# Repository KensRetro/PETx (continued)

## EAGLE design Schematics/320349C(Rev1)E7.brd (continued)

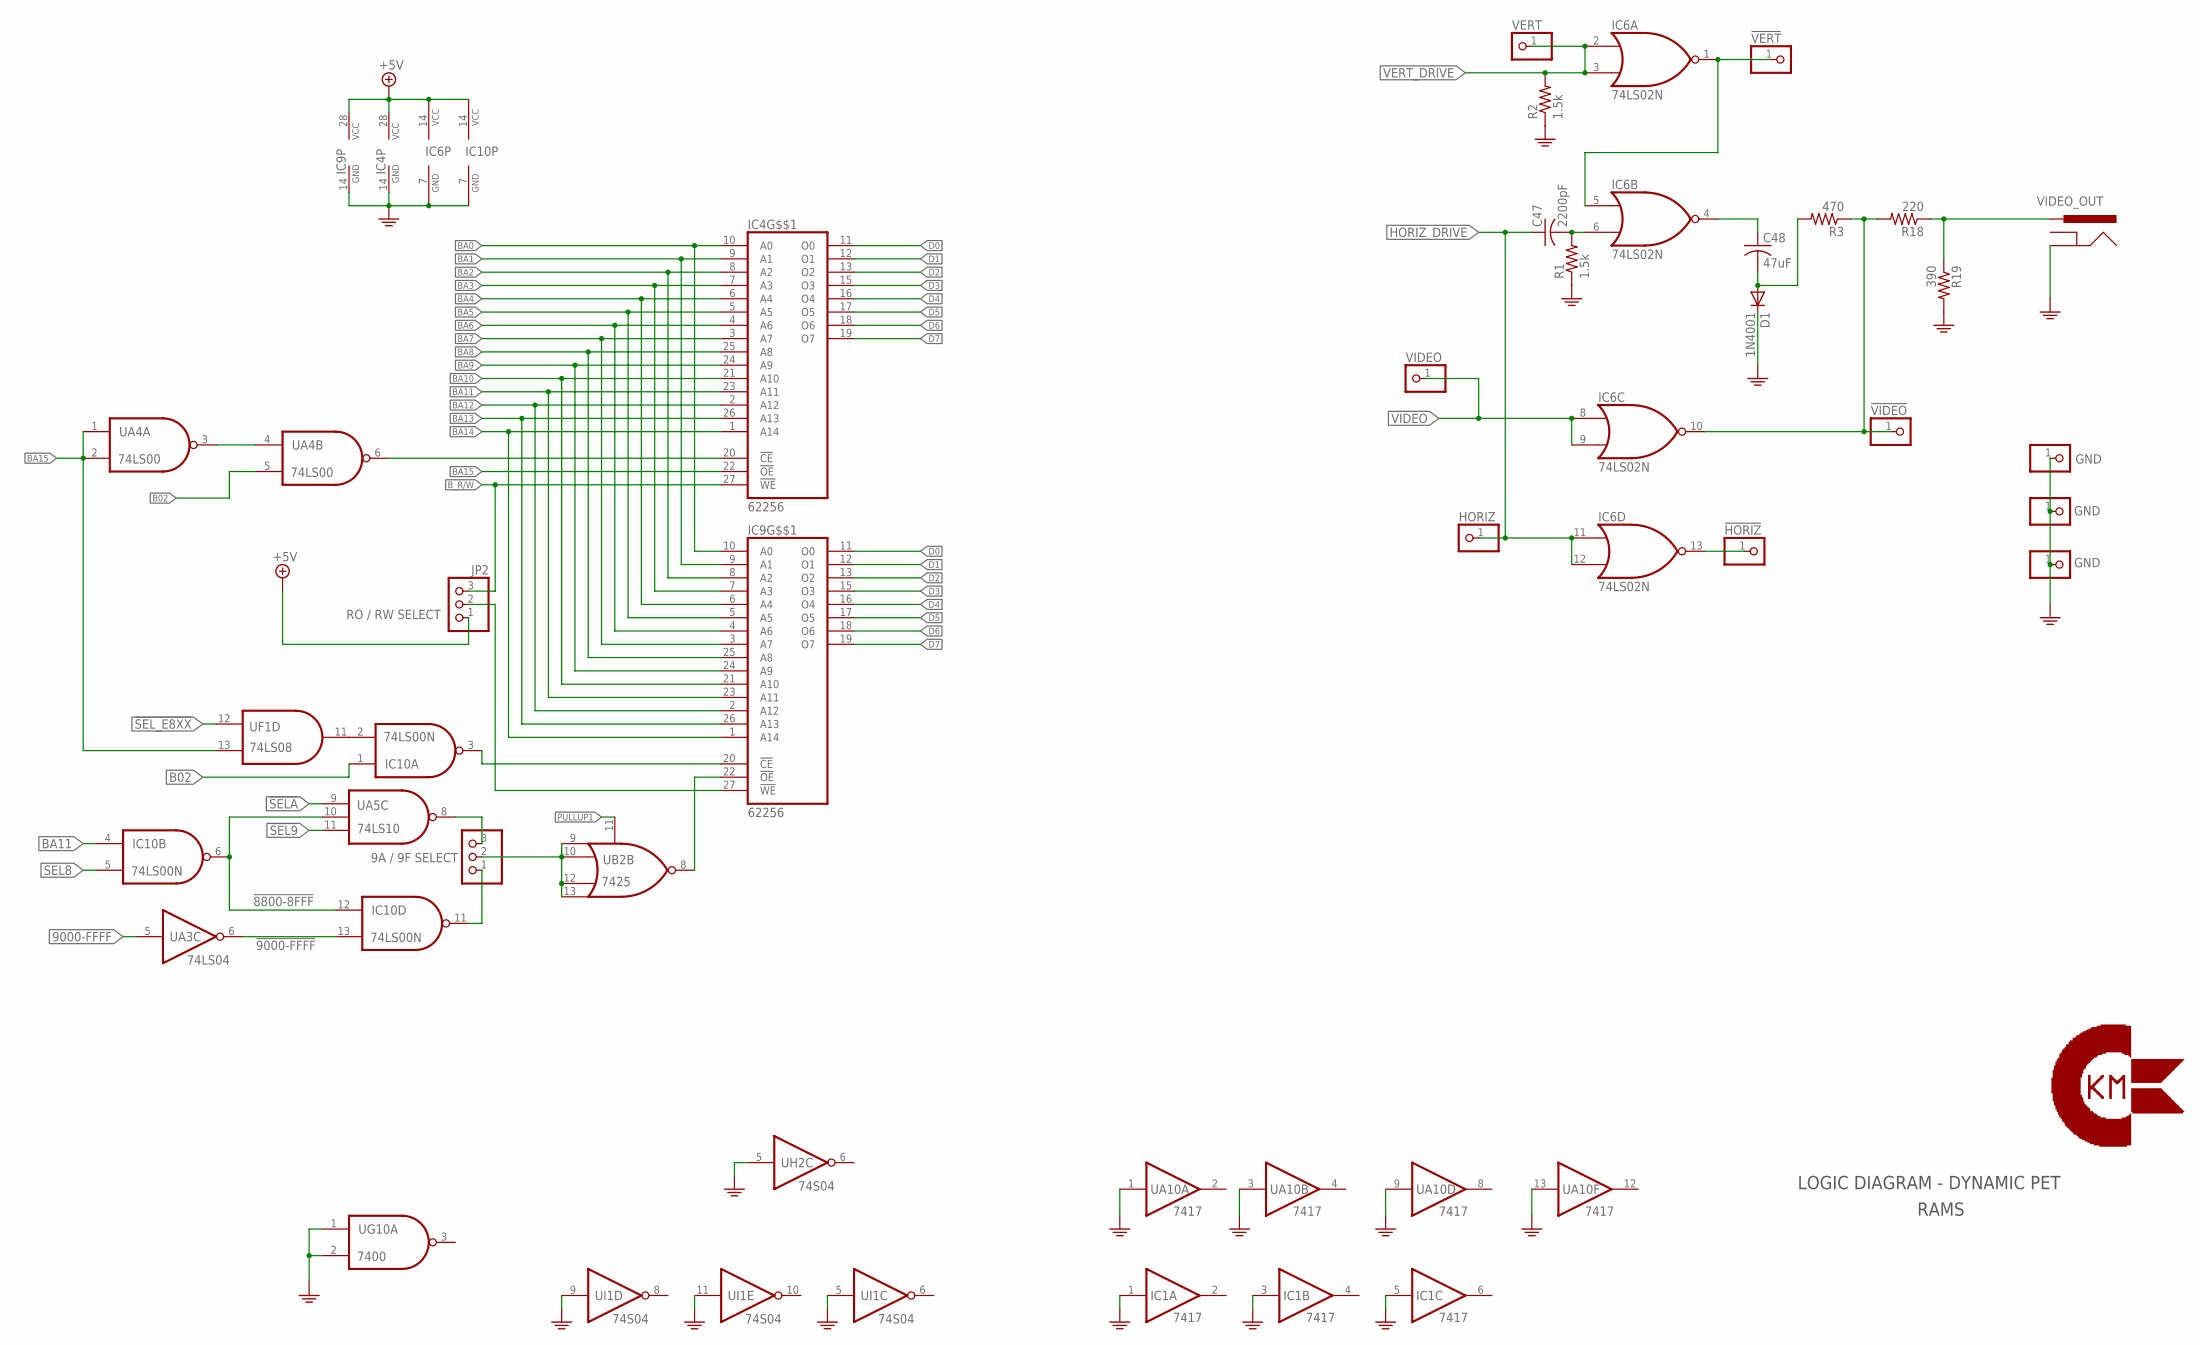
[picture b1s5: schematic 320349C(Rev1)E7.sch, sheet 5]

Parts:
!HORIZ: PINHD-1X1; 1X01
!VERT: PINHD-1X1; 1X01
!VIDEO: PINHD-1X1; 1X01
C47: 2200pF; C025-025X050
C48: 47uF; C050-035X075
D1: 1N4001; DO41-10
HGND: GND; 1X01
HORIZ: PINHD-1X1; 1X01
IC1: 7417; DIL14
IC4, IC9: 62256; DIL28
IC6: 74LS02N; DIL14
IC10: 74LS00N; DIL14
JP2: RO / RW SELECT; 1X03
JP3: 9A / 9F SELECT; 1X03
R1, R2: 1.5k; 0207/10
R3: 470; 0207/10
R18: 220; 0207/10
R19: 390; 0207/10
UA3: 74LS04; DIL14
UA4: 74LS00; DIL14
UA5: 74LS10; DIL14
UA10: 7417; DIL14
UB2: 7425; DIL14
UF1: 74LS08; DIL14
UG10: 7400; DIL14
UH2: 74S04; DIL14
UI1: 74S04; DIL14
VDGND: GND; 1X01
VERT: PINHD-1X1; 1X01
VGND: GND; 1X01
VIDEO: PINHD-1X1; 1X01
VIDEO_OUT: POWER_JACKRCA; RCA

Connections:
9000-FFFF: UA3.5 (I); also elsewhere on the board
!8800-8FFF: IC10.6 (O), IC10.12 (I0), UA5.10 (I1)
!9000-FFFF: IC10.13 (I1), UA3.6 (O)
!SEL9: UA5.11 (I2); also elsewhere on the board
!SELA: UA5.9 (I0); also elsewhere on the board
!SEL_E8XX: UF1.12 (I0); also elsewhere on the board
+5V: IC4.28 (VCC), IC6.14 (VCC), IC9.28 (VCC), IC10.14 (VCC), JP2.1; also elsewhere on the board
B02: IC10.1 (I0), UA4.5 (I1); also elsewhere on the board
BA0: IC4.10 (A0), IC9.10 (A0); also elsewhere on the board
BA1: IC4.9 (A1), IC9.9 (A1); also elsewhere on the board
BA2: IC4.8 (A2), IC9.8 (A2); also elsewhere on the board
BA3: IC4.7 (A3), IC9.7 (A3); also elsewhere on the board
BA4: IC4.6 (A4), IC9.6 (A4); also elsewhere on the board
BA5: IC4.5 (A5), IC9.5 (A5); also elsewhere on the board
BA6: IC4.4 (A6), IC9.4 (A6); also elsewhere on the board
BA7: IC4.3 (A7), IC9.3 (A7); also elsewhere on the board
BA8: IC4.25 (A8), IC9.25 (A8); also elsewhere on the board
BA9: IC4.24 (A9), IC9.24 (A9); also elsewhere on the board
BA10: IC4.21 (A10), IC9.21 (A10); also elsewhere on the board
BA11: IC4.23 (A11), IC9.23 (A11), IC10.4 (I0); also elsewhere on the board
BA12: IC4.2 (A12), IC9.2 (A12); also elsewhere on the board
BA13: IC4.26 (A13), IC9.26 (A13); also elsewhere on the board
BA14: IC4.1 (A14), IC9.1 (A14); also elsewhere on the board
BA15: IC4.22 (!OE), UA4.1 (I0), UA4.2 (I1), UF1.13 (I1); also elsewhere on the board
B_R/W: IC4.27 (!WE), JP2.3; also elsewhere on the board
D0: IC4.11 (O0), IC9.11 (O0); also elsewhere on the board
D1: IC4.12 (O1), IC9.12 (O1); also elsewhere on the board
D2: IC4.13 (O2), IC9.13 (O2); also elsewhere on the board
D3: IC4.15 (O3), IC9.15 (O3); also elsewhere on the board
D4: IC4.16 (O4), IC9.16 (O4); also elsewhere on the board
D5: IC4.17 (O5), IC9.17 (O5); also elsewhere on the board
D6: IC4.18 (O6), IC9.18 (O6); also elsewhere on the board
D7: IC4.19 (O7), IC9.19 (O7); also elsewhere on the board
GND: D1.C, HGND.1, IC1.1 (I), IC1.3 (I), IC1.5 (I), IC4.14 (GND), IC6.7 (GND), IC9.14 (GND), IC10.7 (GND), R1.1, R2.1, R19.2, UA10.1 (I), UA10.3 (I), UA10.9 (I), UA10.13 (I), UG10.1 (I0), UG10.2 (I1), UH2.5 (I), UI1.5 (I), UI1.9 (I), UI1.11 (I), VDGND.1, VGND.1, VIDEO_OUT.BARREL (GND); also elsewhere on the board
HORIZ_DRIVE: C47.1, HORIZ.1, IC6.11 (I0), IC6.12 (I1); also elsewhere on the board
unnamed: JP3.3, UA5.8 (O)
unnamed: !VERT.1, IC6.1 (O), IC6.5 (I0)
unnamed: IC10.2 (I1), UF1.11 (O)
unnamed: R18.1, R19.1, VIDEO_OUT.BREAK (PWR)
unnamed: C47.2, IC6.6 (I1), R1.2
unnamed: IC9.22 (!OE), UB2.8 (O)
unnamed: !VIDEO.1, IC6.10 (O), R3.1, R18.2
unnamed: JP3.2, UB2.9 (I0), UB2.10 (I1), UB2.12 (I2), UB2.13 (I3)
unnamed: C48.1, IC6.4 (O)
unnamed: C48.2, D1.A, R3.2
unnamed: IC9.20 (!CE), IC10.3 (O)
unnamed: IC9.27 (!WE), JP2.2
unnamed: !HORIZ.1, IC6.13 (O)
unnamed: IC4.20 (!CE), UA4.6 (O)
unnamed: IC10.11 (O), JP3.1
unnamed: UA4.3 (O), UA4.4 (I0)
PULLUP1: UB2.11 (G); also elsewhere on the board
SEL8: IC10.5 (I1); also elsewhere on the board
VERT_DRIVE: IC6.2 (I0), IC6.3 (I1), R2.2, VERT.1; also elsewhere on the board
VIDEO: IC6.8 (I0), IC6.9 (I1), VIDEO.1; also elsewhere on the board

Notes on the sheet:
LOGIC DIAGRAM - DYNAMIC PET
RAMS

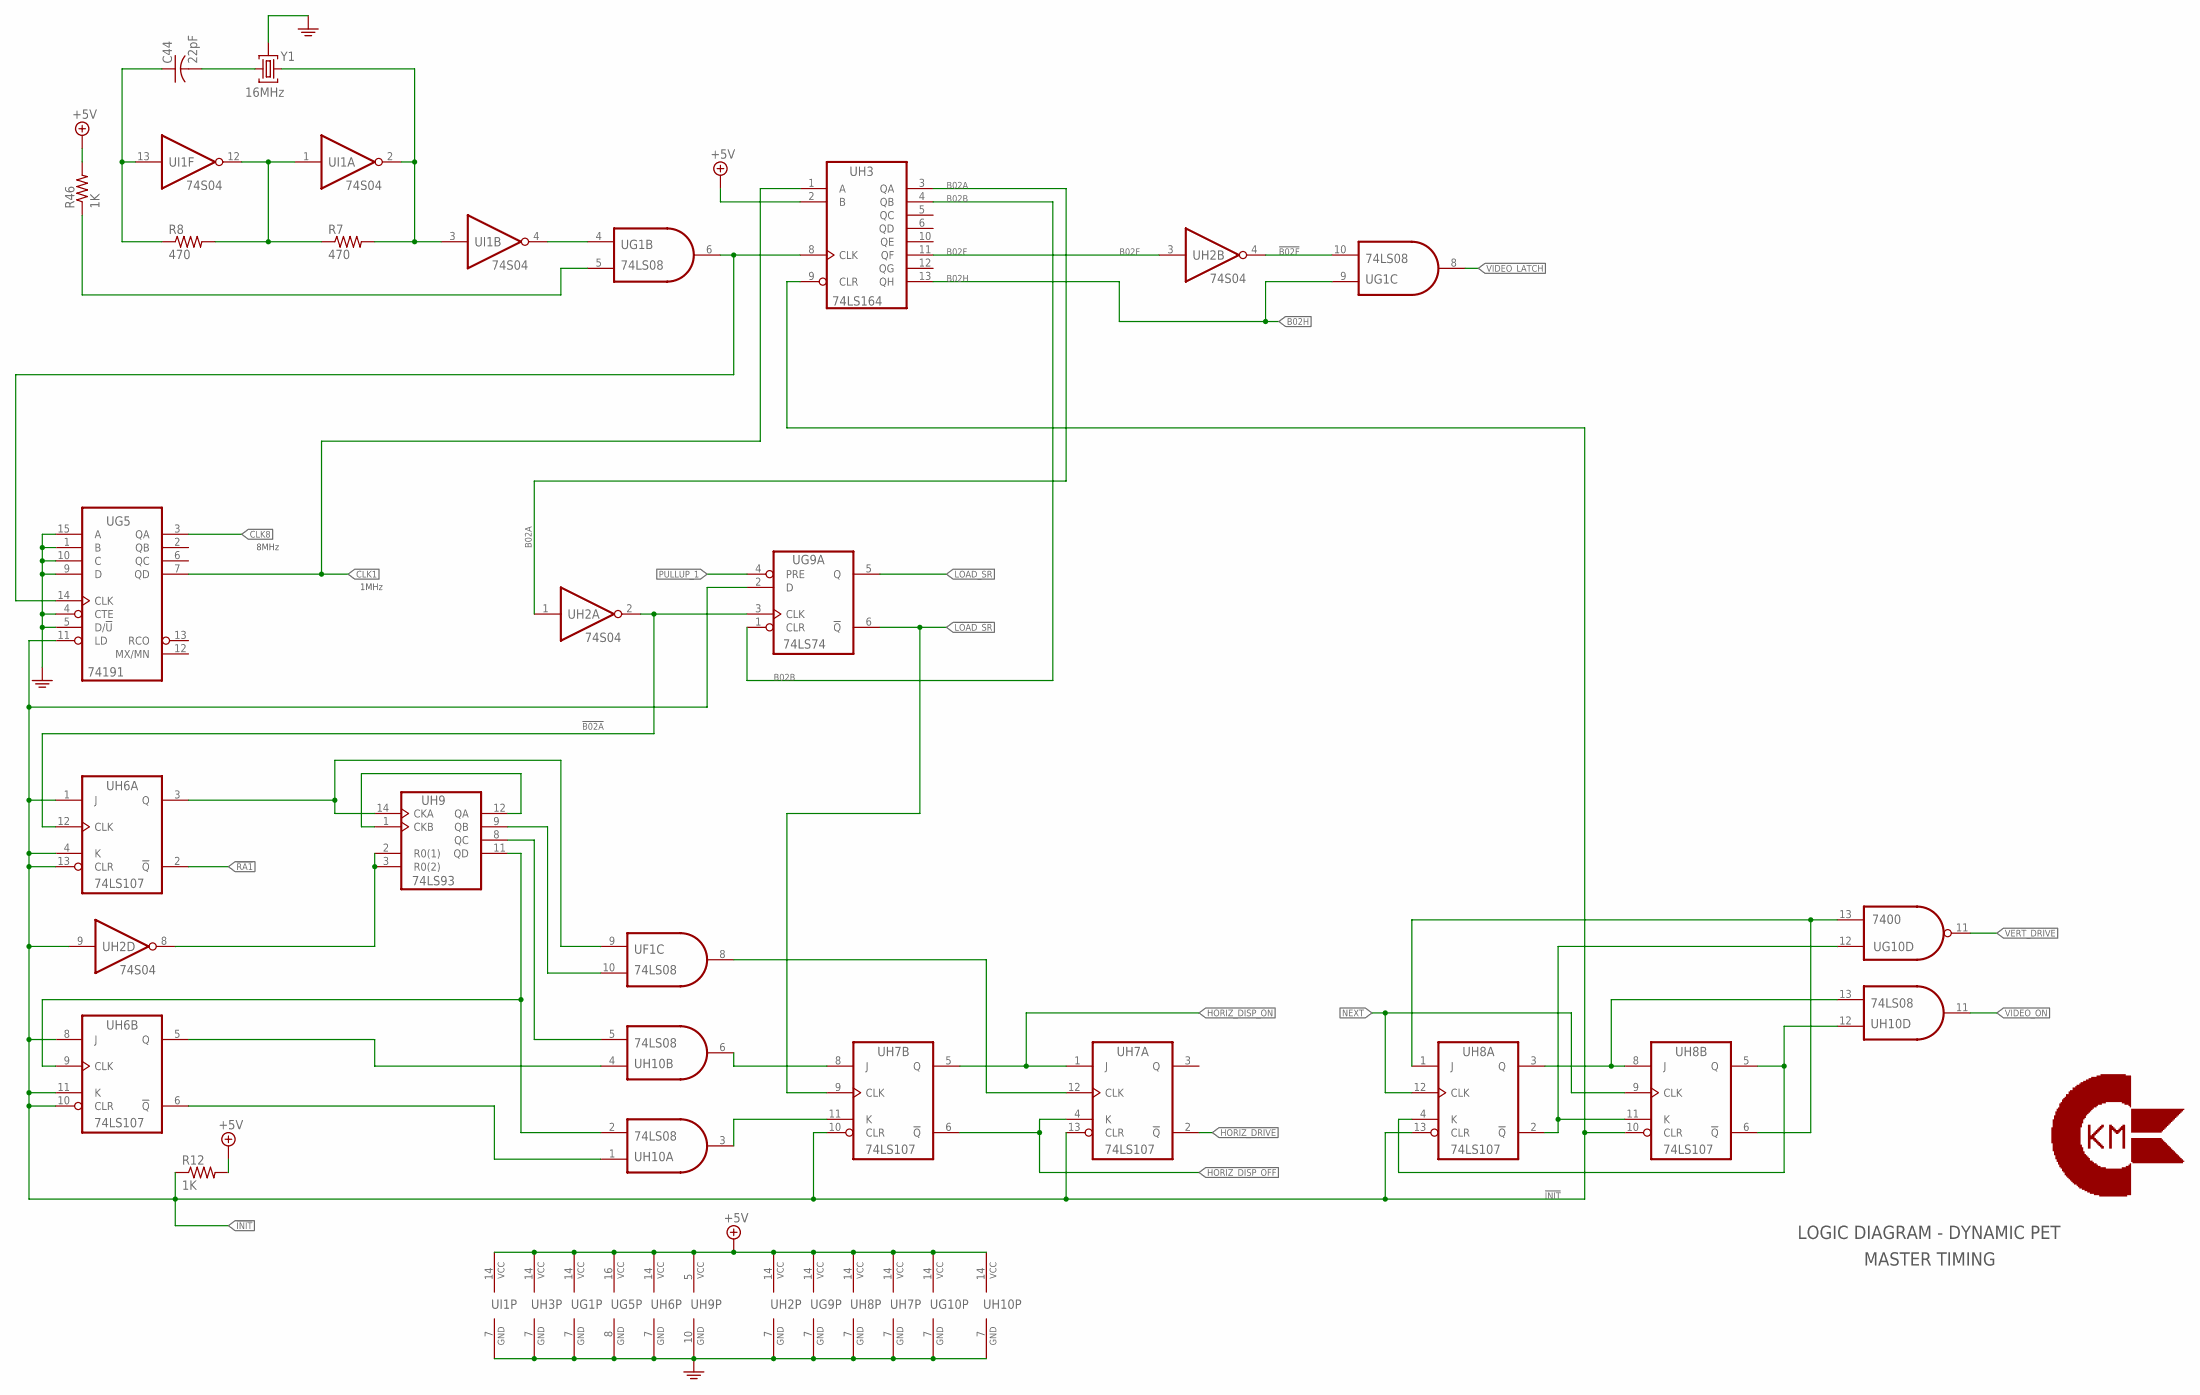
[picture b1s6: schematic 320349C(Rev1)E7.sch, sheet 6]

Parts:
C44: 22pF; C050-035X075
R7, R8: 470; 0207/10
R12, R46: 1K; 0207/10
UF1: 74LS08; DIL14
UG1: 74LS08; DIL14
UG5: 74191; DIL16
UG9: 74LS74; DIL14
UG10: 7400; DIL14
UH2: 74S04; DIL14
UH3: 74LS164; DIL14
UH6, UH7, UH8: 74LS107; DIL14
UH9: 74LS93; DIL14
UH10: 74LS08; DIL14
UI1: 74S04; DIL14
Y1: 16MHz; HC49TL-H

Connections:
!B02A: UG9.3 (CLK), UH2.2 (O), UH6.12 (CLK)
!B02F: UG1.10 (I1), UH2.4 (O)
!INIT: R12.1, UG5.11 (LD), UG9.2 (D), UH2.9 (I), UH3.9 (CLR), UH6.1 (J), UH6.4 (K), UH6.8 (J), UH6.10 (CLR), UH6.11 (K), UH6.13 (CLR), UH7.10 (CLR), UH7.13 (CLR), UH8.10 (CLR), UH8.13 (CLR); also elsewhere on the board
!LOAD_SR: UG9.6 (!Q), UH7.9 (CLK); also elsewhere on the board
!RA1: UH6.2 (!Q); also elsewhere on the board
+5V: R12.2, R46.2, UG1.14 (VCC), UG5.16 (VCC), UG9.14 (VCC), UG10.14 (VCC), UH2.14 (VCC), UH3.2 (B), UH3.14 (VCC), UH6.14 (VCC), UH7.14 (VCC), UH8.14 (VCC), UH9.5 (VCC), UH10.14 (VCC), UI1.14 (VCC); also elsewhere on the board
B02A: UH2.1 (I), UH3.3 (QA)
B02B: UG9.1 (CLR), UH3.4 (QB)
B02F: UH2.3 (I), UH3.11 (QF)
B02H: UG1.9 (I0), UH3.13 (QH); also elsewhere on the board
CLK1: UG5.7 (QD), UH3.1 (A); also elsewhere on the board
CLK8: UG5.3 (QA); also elsewhere on the board
GND: UG1.7 (GND), UG5.1 (B), UG5.4 (CTE), UG5.5 (D/!U), UG5.8 (GND), UG5.9 (D), UG5.10 (C), UG5.15 (A), UG9.7 (GND), UG10.7 (GND), UH2.7 (GND), UH3.7 (GND), UH6.7 (GND), UH7.7 (GND), UH8.7 (GND), UH9.10 (GND), UH10.7 (GND), UI1.7 (GND), Y1.3; also elsewhere on the board
HORIZ_DISP_OFF: UH7.4 (K), UH7.6 (!Q); also elsewhere on the board
HORIZ_DISP_ON: UH7.1 (J), UH7.5 (Q); also elsewhere on the board
HORIZ_DRIVE: UH7.2 (!Q); also elsewhere on the board
LOAD_SR: UG9.5 (Q); also elsewhere on the board
unnamed: C44.2, Y1.2
unnamed: C44.1, R8.1, UI1.13 (I)
unnamed: UG1.6 (O), UG5.14 (CLK), UH3.8 (CLK)
unnamed: R7.2, UI1.2 (O), UI1.3 (I), Y1.1
unnamed: UG1.4 (I0), UI1.4 (O)
unnamed: UH6.6 (!Q), UH10.1 (I0)
unnamed: UF1.8 (O), UH7.12 (CLK)
unnamed: UH2.8 (O), UH9.2 (R0(1)), UH9.3 (R0(2))
unnamed: UH7.11 (K), UH10.3 (O)
unnamed: UH7.8 (J), UH10.6 (O)
unnamed: UH8.3 (Q), UH8.8 (J), UH10.13 (I1)
unnamed: UG10.12 (I0), UH8.2 (!Q), UH8.11 (K)
unnamed: UH8.4 (K), UH8.5 (Q), UH10.12 (I0)
unnamed: UG10.13 (I1), UH8.1 (J), UH8.6 (!Q)
NEXT: UH8.9 (CLK), UH8.12 (CLK); also elsewhere on the board
PULLUP_1: UG9.4 (PRE); also elsewhere on the board
RA1: UF1.9 (I0), UH6.3 (Q), UH9.14 (CKA)
RA2: UH9.1 (CKB), UH9.12 (QA)
RA3: UF1.10 (I1), UH9.9 (QB)
RA4: UH9.8 (QC), UH10.5 (I1)
RA5: UH6.9 (CLK), UH9.11 (QD), UH10.2 (I1)
RA6: UH6.5 (Q), UH10.4 (I0)
TP8: R46.1, UG1.5 (I1)
TP9: R7.1, R8.2, UI1.1 (I), UI1.12 (O)
VERT_DRIVE: UG10.11 (O); also elsewhere on the board
VIDEO_LATCH: UG1.8 (O); also elsewhere on the board
VIDEO_ON: UH10.11 (O); also elsewhere on the board

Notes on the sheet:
LOGIC DIAGRAM - DYNAMIC PET
MASTER TIMING
8MHz
1MHz

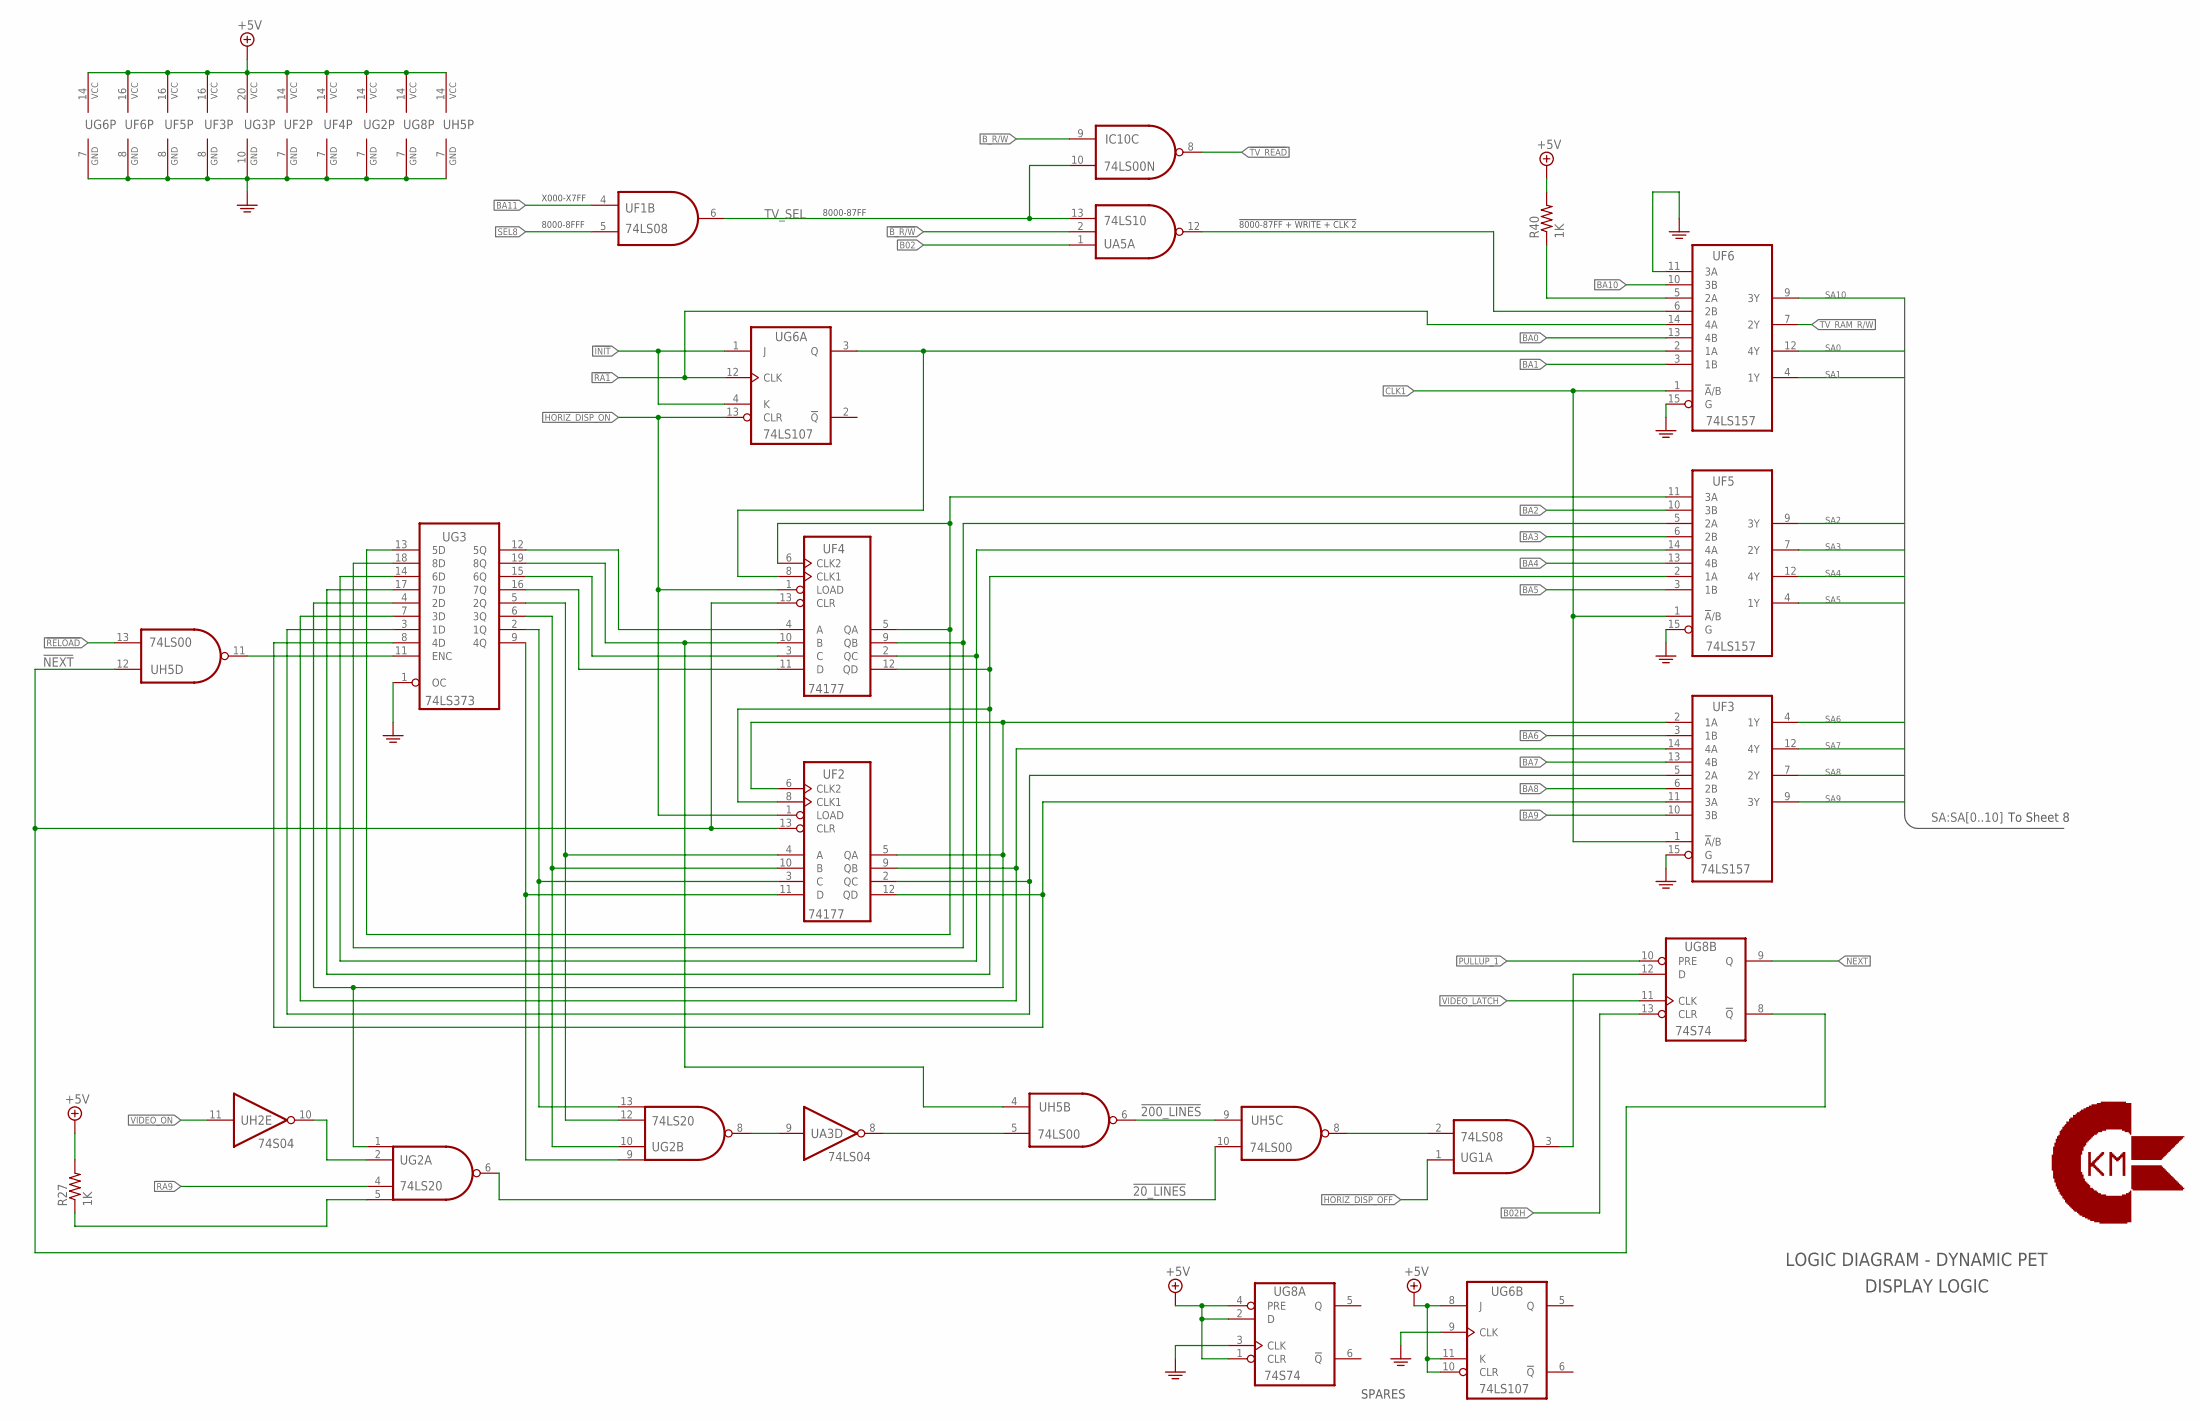
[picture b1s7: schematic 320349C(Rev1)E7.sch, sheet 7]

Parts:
IC10: 74LS00N; DIL14
R27, R40: 1K; 0207/10
UA3: 74LS04; DIL14
UA5: 74LS10; DIL14
UF1: 74LS08; DIL14
UF2, UF4: 74177; DIL14
UF3, UF5, UF6: 74LS157; DIL16
UG1: 74LS08; DIL14
UG2: 74LS20; DIL14
UG3: 74LS373; DIL20
UG6: 74LS107; DIL14
UG8: 74S74; DIL14
UH2: 74S04; DIL14
UH5: 74LS00; DIL14

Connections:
!20_LINES: UG2.6 (O), UH5.10 (I1)
!200_LINES: UH5.6 (O), UH5.9 (I0)
!BA11: UF1.4 (I0); also elsewhere on the board
!B_R/W: UA5.2 (I1); also elsewhere on the board
!INIT: UG6.1 (J), UG6.4 (K); also elsewhere on the board
!NEXT: UF2.13 (CLR), UF4.13 (CLR), UG8.8 (!Q), UH5.12 (I0)
!RA1: UF6.14 (4A), UG6.12 (CLK); also elsewhere on the board
!RELOAD: UH5.13 (I1); also elsewhere on the board
!TV_READ: IC10.8 (O); also elsewhere on the board
+5V: R27.2, R40.2, UF2.14 (VCC), UF3.16 (VCC), UF4.14 (VCC), UF5.16 (VCC), UF6.16 (VCC), UG2.14 (VCC), UG3.20 (VCC), UG6.8 (J), UG6.10 (CLR), UG6.11 (K), UG6.14 (VCC), UG8.1 (CLR), UG8.2 (D), UG8.4 (PRE), UG8.14 (VCC), UH5.14 (VCC); also elsewhere on the board
B02: UA5.1 (I0); also elsewhere on the board
B02H: UG8.13 (CLR); also elsewhere on the board
BA0: UF6.13 (4B); also elsewhere on the board
BA1: UF6.3 (1B); also elsewhere on the board
BA2: UF5.10 (3B); also elsewhere on the board
BA3: UF5.6 (2B); also elsewhere on the board
BA4: UF5.13 (4B); also elsewhere on the board
BA5: UF5.3 (1B); also elsewhere on the board
BA6: UF3.3 (1B); also elsewhere on the board
BA7: UF3.13 (4B); also elsewhere on the board
BA8: UF3.6 (2B); also elsewhere on the board
BA9: UF3.10 (3B); also elsewhere on the board
BA10: UF6.10 (3B); also elsewhere on the board
B_R/W: IC10.9 (I0); also elsewhere on the board
CLK1: UF3.1 (!A!/B), UF5.1 (!A!/B), UF6.1 (!A!/B); also elsewhere on the board
GND: UF2.7 (GND), UF3.8 (GND), UF3.15 (G), UF4.7 (GND), UF5.8 (GND), UF5.15 (G), UF6.8 (GND), UF6.11 (3A), UF6.15 (G), UG2.7 (GND), UG3.1 (OC), UG3.10 (GND), UG6.7 (GND), UG6.9 (CLK), UG8.3 (CLK), UG8.7 (GND), UH5.7 (GND); also elsewhere on the board
HORIZ_DISP_OFF: UG1.1 (I0); also elsewhere on the board
HORIZ_DISP_ON: UF2.1 (LOAD), UF4.1 (LOAD), UG6.13 (CLR); also elsewhere on the board
unnamed: UF4.5 (QA), UF4.6 (CLK2), UF5.11 (3A), UG3.13 (5D)
unnamed: UF4.9 (QB), UF5.5 (2A), UG3.18 (8D)
unnamed: UF4.2 (QC), UF5.14 (4A), UG3.14 (6D)
unnamed: UF2.8 (CLK1), UF4.12 (QD), UF5.2 (1A), UG3.17 (7D)
unnamed: UF2.5 (QA), UF2.6 (CLK2), UF3.2 (1A), UG2.1 (I0), UG3.4 (2D)
unnamed: UF2.9 (QB), UF3.14 (4A), UG3.7 (3D)
unnamed: R40.1, UF6.5 (2A)
unnamed: UA5.12 (O), UF6.6 (2B)
unnamed: UF4.8 (CLK1), UF6.2 (1A), UG6.3 (Q)
unnamed: UF2.2 (QC), UF3.5 (2A), UG3.3 (1D)
unnamed: UF2.12 (QD), UF3.11 (3A), UG3.8 (4D)
unnamed: UF2.11 (D), UG2.9 (I0), UG3.9 (4Q)
unnamed: UF2.3 (C), UG2.13 (I3), UG3.2 (1Q)
unnamed: UF2.10 (B), UG2.10 (I1), UG3.6 (3Q)
unnamed: UF2.4 (A), UG2.12 (I2), UG3.5 (2Q)
unnamed: UF4.11 (D), UG3.16 (7Q)
unnamed: UF4.3 (C), UG3.15 (6Q)
unnamed: UF4.10 (B), UG3.19 (8Q), UH5.4 (I0)
unnamed: UF4.4 (A), UG3.12 (5Q)
unnamed: UG1.3 (O), UG8.12 (D)
unnamed: UG1.2 (I1), UH5.8 (O)
unnamed: UA3.8 (O), UH5.5 (I1)
unnamed: UA3.9 (I), UG2.8 (O)
unnamed: UG3.11 (ENC), UH5.11 (O)
unnamed: UG2.2 (I1), UH2.10 (O)
NEXT: UG8.9 (Q); also elsewhere on the board
PULLUP_1: UG8.10 (PRE); also elsewhere on the board
PULLUP_2: R27.1, UG2.5 (I3)
RA9: UG2.4 (I2); also elsewhere on the board
SA0: UF6.12 (4Y); also elsewhere on the board
SA1: UF6.4 (1Y); also elsewhere on the board
SA2: UF5.9 (3Y); also elsewhere on the board
SA3: UF5.7 (2Y); also elsewhere on the board
SA4: UF5.12 (4Y); also elsewhere on the board
SA5: UF5.4 (1Y); also elsewhere on the board
SA6: UF3.4 (1Y); also elsewhere on the board
SA7: UF3.12 (4Y); also elsewhere on the board
SA8: UF3.7 (2Y); also elsewhere on the board
SA9: UF3.9 (3Y); also elsewhere on the board
SA10: UF6.9 (3Y); also elsewhere on the board
SEL8: UF1.5 (I1); also elsewhere on the board
TV_RAM_R/W: UF6.7 (2Y); also elsewhere on the board
TV_SEL: IC10.10 (I1), UA5.13 (I2), UF1.6 (O)
VIDEO_LATCH: UG8.11 (CLK); also elsewhere on the board
VIDEO_ON: UH2.11 (I); also elsewhere on the board

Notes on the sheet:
LOGIC DIAGRAM - DYNAMIC PET
DISPLAY LOGIC
To Sheet 8
SPARES
X000-X7FF
8000-8FFF
8000-87FF
!8000-87FF + WRITE + CLK 2

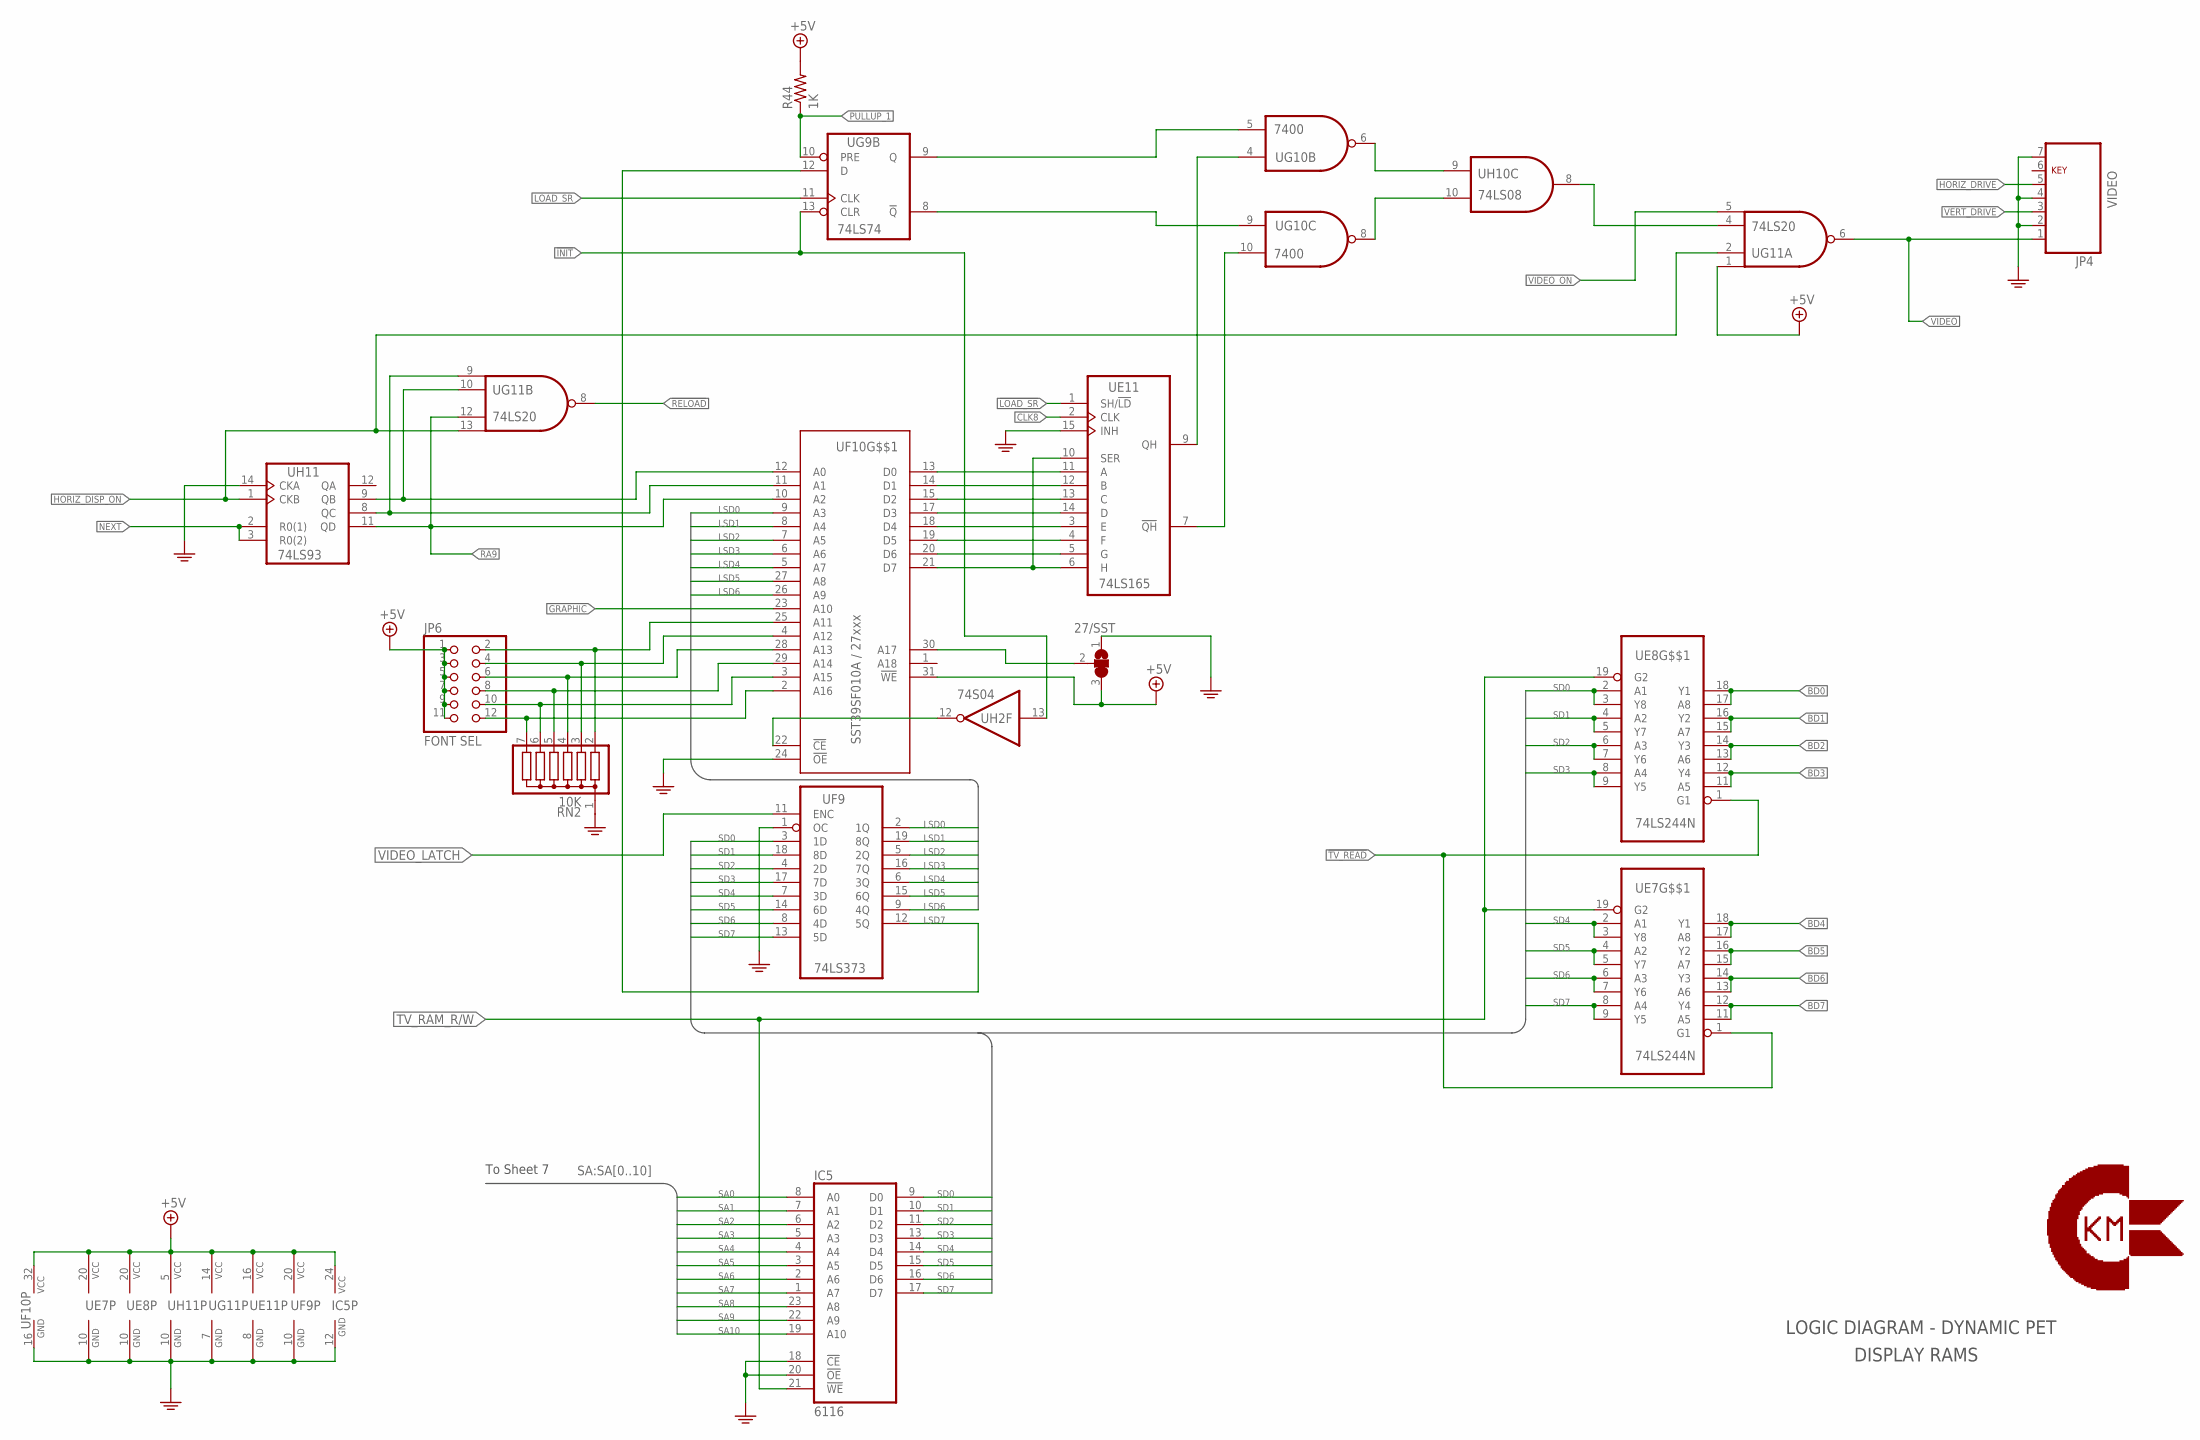
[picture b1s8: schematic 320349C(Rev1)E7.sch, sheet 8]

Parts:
IC5: 6116; DIL24
JP4: VIDEO; 1X07
JP6: FONT SEL; 2X06
R44: 1K; 0207/10
RN2: 10K; SIL7
SJ1: 27/SST; SJ_2
UE7, UE8: 74LS244N; DIL20
UE11: 74LS165; DIL16
UF9: 74LS373; DIL20
UF10: SST39SF010A / 27xxx; SST39SF010A
UG9: 74LS74; DIL14
UG10: 7400; DIL14
UG11: 74LS20; DIL14
UH2: 74S04; DIL14
UH10: 74LS08; DIL14
UH11: 74LS93; DIL14

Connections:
!INIT: UG9.13 (CLR), UH2.13 (I); also elsewhere on the board
!LOAD_SR: UE11.1 (SH/!LD); also elsewhere on the board
!RELOAD: UG11.8 (O); also elsewhere on the board
!TV_READ: UE7.1 (G1), UE8.1 (G1); also elsewhere on the board
+5V: IC5.24 (VCC), JP6.1, JP6.3, JP6.5, JP6.7, JP6.9, JP6.11, R44.2, SJ1.3, UE7.20 (VCC), UE8.20 (VCC), UE11.16 (VCC), UF9.20 (VCC), UF10.31 (!WE), UF10.32 (VCC), UG11.1 (I0), UG11.14 (VCC), UH11.5 (VCC); also elsewhere on the board
BD0: UE8.17 (A8), UE8.18 (Y1); also elsewhere on the board
BD1: UE8.15 (A7), UE8.16 (Y2); also elsewhere on the board
BD2: UE8.13 (A6), UE8.14 (Y3); also elsewhere on the board
BD3: UE8.11 (A5), UE8.12 (Y4); also elsewhere on the board
BD4: UE7.17 (A8), UE7.18 (Y1); also elsewhere on the board
BD5: UE7.15 (A7), UE7.16 (Y2); also elsewhere on the board
BD6: UE7.13 (A6), UE7.14 (Y3); also elsewhere on the board
BD7: UE7.11 (A5), UE7.12 (Y4); also elsewhere on the board
CLK8: UE11.2 (CLK); also elsewhere on the board
GND: IC5.12 (GND), IC5.18 (!CE), IC5.20 (!OE), JP4.2, JP4.4, JP4.7, RN2.1, SJ1.1, UE7.10 (GND), UE8.10 (GND), UE11.8 (GND), UE11.15 (INH), UF9.1 (OC), UF9.10 (GND), UF10.16 (GND), UF10.24 (!OE), UG11.7 (GND), UH11.10 (GND), UH11.14 (CKA); also elsewhere on the board
GRAPHIC: UF10.23 (A10); also elsewhere on the board
HORIZ_DISP_ON: UG11.2 (I1), UG11.13 (I3), UH11.1 (CKB); also elsewhere on the board
HORIZ_DRIVE: JP4.5; also elsewhere on the board
LOAD_SR: UG9.11 (CLK); also elsewhere on the board
LSD0: UF9.2 (1Q), UF10.9 (A3)
LSD1: UF9.19 (8Q), UF10.8 (A4)
LSD2: UF9.5 (2Q), UF10.7 (A5)
LSD3: UF9.16 (7Q), UF10.6 (A6)
LSD4: UF9.6 (3Q), UF10.5 (A7)
LSD5: UF9.15 (6Q), UF10.27 (A8)
LSD6: UF9.9 (4Q), UF10.26 (A9)
LSD7: UF9.12 (5Q), UG9.12 (D)
unnamed: UF10.22 (!CE), UH2.12 (O)
unnamed: JP6.2, RN2.2, UF10.25 (A11)
unnamed: JP6.4, RN2.3, UF10.4 (A12)
unnamed: JP6.6, RN2.4, UF10.28 (A13)
unnamed: JP6.8, RN2.5, UF10.29 (A14)
unnamed: UF10.11 (A1), UG11.9 (I0), UH11.8 (QC)
unnamed: JP6.10, RN2.6, UF10.3 (A15)
unnamed: JP6.12, RN2.7, UF10.2 (A16)
unnamed: SJ1.2, UF10.30 (A17)
unnamed: UG11.4 (I2), UH10.8 (O)
unnamed: UG9.9 (Q), UG10.5 (I1)
unnamed: UG9.8 (!Q), UG10.9 (I0)
unnamed: UG10.8 (O), UH10.10 (I1)
unnamed: UG10.6 (O), UH10.9 (I0)
unnamed: UE11.7 (!QH), UG10.10 (I1)
unnamed: UE11.9 (QH), UG10.4 (I0)
unnamed: UE11.11 (A), UF10.13 (D0)
unnamed: UE11.12 (B), UF10.14 (D1)
unnamed: UE11.13 (C), UF10.15 (D2)
unnamed: UE11.14 (D), UF10.17 (D3)
unnamed: UE11.3 (E), UF10.18 (D4)
unnamed: UE11.4 (F), UF10.19 (D5)
unnamed: UE11.5 (G), UF10.20 (D6)
unnamed: UE11.6 (H), UE11.10 (SER), UF10.21 (D7)
NEXT: UH11.2 (R0(1)), UH11.3 (R0(2)); also elsewhere on the board
PULLUP_1: R44.1, UG9.10 (PRE); also elsewhere on the board
RA7: UF10.12 (A0), UG11.10 (I1), UH11.9 (QB)
RA9: UF10.10 (A2), UG11.12 (I2), UH11.11 (QD); also elsewhere on the board
SA0: IC5.8 (A0); also elsewhere on the board
SA1: IC5.7 (A1); also elsewhere on the board
SA2: IC5.6 (A2); also elsewhere on the board
SA3: IC5.5 (A3); also elsewhere on the board
SA4: IC5.4 (A4); also elsewhere on the board
SA5: IC5.3 (A5); also elsewhere on the board
SA6: IC5.2 (A6); also elsewhere on the board
SA7: IC5.1 (A7); also elsewhere on the board
SA8: IC5.23 (A8); also elsewhere on the board
SA9: IC5.22 (A9); also elsewhere on the board
SA10: IC5.19 (A10); also elsewhere on the board
SD0: IC5.9 (D0), UE8.2 (A1), UE8.3 (Y8), UF9.3 (1D)
SD1: IC5.10 (D1), UE8.4 (A2), UE8.5 (Y7), UF9.18 (8D)
SD2: IC5.11 (D2), UE8.6 (A3), UE8.7 (Y6), UF9.4 (2D)
SD3: IC5.13 (D3), UE8.8 (A4), UE8.9 (Y5), UF9.17 (7D)
SD4: IC5.14 (D4), UE7.2 (A1), UE7.3 (Y8), UF9.7 (3D)
SD5: IC5.15 (D5), UE7.4 (A2), UE7.5 (Y7), UF9.14 (6D)
SD6: IC5.16 (D6), UE7.6 (A3), UE7.7 (Y6), UF9.8 (4D)
SD7: IC5.17 (D7), UE7.8 (A4), UE7.9 (Y5), UF9.13 (5D)
TV_RAM_R/W: IC5.21 (!WE), UE7.19 (G2), UE8.19 (G2); also elsewhere on the board
VERT_DRIVE: JP4.3; also elsewhere on the board
VIDEO: JP4.1, UG11.6 (O); also elsewhere on the board
VIDEO_LATCH: UF9.11 (ENC); also elsewhere on the board
VIDEO_ON: UG11.5 (I3); also elsewhere on the board

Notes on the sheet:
LOGIC DIAGRAM - DYNAMIC PET
DISPLAY RAMS
To Sheet 7
KEY

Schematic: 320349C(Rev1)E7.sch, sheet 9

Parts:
9V: PINHD-1X1; 1X01
+5V: PINHD-1X1; 1X01
+5V1: +5V; 1X01
C1, C2, C3, C4, C5, C6, C7, C8, C9, C10, C11, C12, C13, C18, C19, C20, C21, C22, C23, C24, C25, C26, C27, C28, C29, C30, C31, C32, C33, C34, C35, C36, C37, C38, C39, C40, C41, C42, C45, C46, C49, C50, C51, C52, C53, C54, C55, C56, C77, C78, C79, C80, C91, C92, C93: 0.1uF/50; C025-025X050
C14: 47uF/16; E2,5-6
C17: 1.0uF/25; E1,8-4
CR10: 1N4001; DO41-10
GND2, GND3, GND4: GND; 1X01
J4: POWER_JACKPTH; POWER_JACK_PTH
KEY: Key; 1X01
LED: PINHD-1X2; 1X02
LED1: +9V; LED5MM
LED2: +5V; LED5MM
R20: 470; 0207/10
R21: 220; 0207/10
S1: 320-938; 320-938H
V7805: VREG_78XXL

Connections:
+5V: +5V.1, +5V1.1, C1.1, C2.1, C3.1, C4.1, C5.1, C6.1, C7.1, C8.1, C9.1, C10.1, C11.1, C12.1, C13.1, C14.+, C18.1, C19.1, C20.1, C21.1, C22.1, C23.1, C24.1, C25.1, C26.1, C27.1, C28.1, C29.1, C30.1, C31.1, C32.1, C33.1, C34.1, C35.1, C36.1, C37.1, C38.1, C39.1, C40.1, C41.1, C42.1, C45.1, C46.1, C49.1, C50.1, C51.1, C52.1, C53.1, C54.1, C55.1, C56.1, C77.1, C78.1, C79.1, C80.1, C91.1, C92.1, C93.1, CR10.A, R21.2, V7805.OUT; also elsewhere on the board
+9V_UNREG: 9V.1, C17.+, CR10.C, R20.2, S1.2, S1.5, V7805.IN; also elsewhere on the board
GND: C1.2, C2.2, C3.2, C4.2, C5.2, C6.2, C7.2, C8.2, C9.2, C10.2, C11.2, C12.2, C13.2, C14.-, C17.-, C18.2, C19.2, C20.2, C21.2, C22.2, C23.2, C24.2, C25.2, C26.2, C27.2, C28.2, C29.2, C30.2, C31.2, C32.2, C33.2, C34.2, C35.2, C36.2, C37.2, C38.2, C39.2, C40.2, C41.2, C42.2, C45.2, C46.2, C49.2, C50.2, C51.2, C52.2, C53.2, C54.2, C55.2, C56.2, C77.2, C78.2, C79.2, C80.2, C91.2, C92.2, C93.2, GND2.1, GND3.1, GND4.1, J4.GND, LED.2, LED1.K (C), LED2.K (C), V7805.GND; also elsewhere on the board
unnamed: LED1.A, R20.1
unnamed: LED.1, LED2.A, R21.1
unnamed: J4.PWR, S1.3 (S), S1.6 (S)

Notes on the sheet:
LOGIC DIAGRAM - DYNAMIC PET
VOLTAGE REGULATOR
